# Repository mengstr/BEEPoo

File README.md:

## BEEPoo - Standalone AY3-8912 sound player

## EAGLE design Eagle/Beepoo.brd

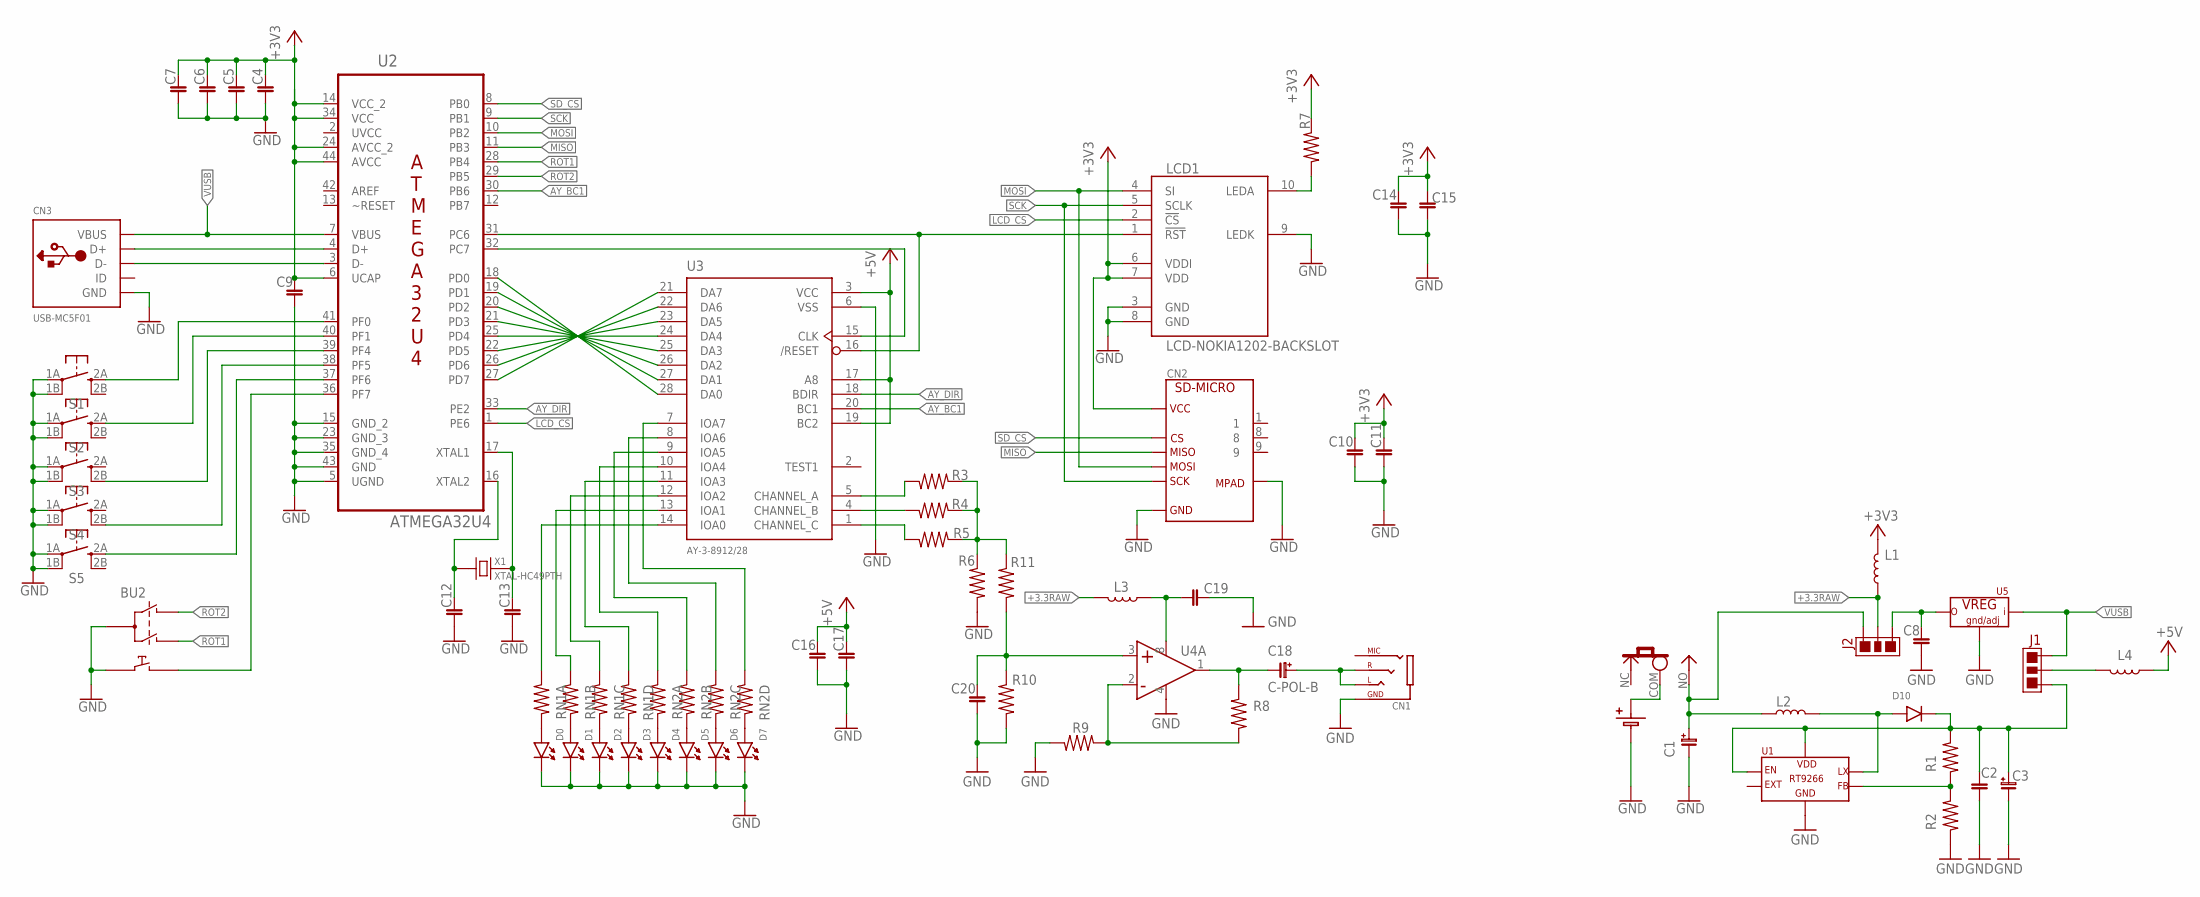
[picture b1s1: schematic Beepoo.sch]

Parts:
BA1: BATTERY2-CR123; BAT-CR123A
BU2: ROTARY
C1: C-POL-C; PANASONIC_C
C2, C4, C5, C6, C7, C11, C12, C13, C15, C17, C20: C-0805; C0805
C3: EEEFK0J101UR; PANASONIC_C
C8, C9, C10, C14, C16, C19: 1u; C0805
C18: C-POL-B; PANASONIC_B
CN1: JACK4PTH; PJ320E
CN2: SD-MICRO; SD-TFP09
CN3: USB-MC5F01; USB-MICRO-MC5F01
D0, D1, D2, D3, D4, D5, D6, D7: LED-0805; LED0805
D10: DIODE-SOD123; SOD123
J1, J2: JUMPER3-1.5MM; JP3-1.5MM
L1, L3, L4: L-0805; L0805
L2: L-BOURNS-SRP7030; IND-BOURNS-SRP7030
LCD1: LCD-NOKIA1202-BACKSLOT; NOKIA1202LCD-BACK-SLOT
R1, R2, R3, R4, R5, R6, R7, R8, R9, R10, R11: R-0805; R0805
RN1, RN2: R-ARR4; RN8P-4R-CRA06S
S1, S2, S3, S4, S5: SWITCH2-12X12PTH; TACT12X12-PTH
SW2: SLIDE1-PCM12; SW-PCM12
U1: RT9266-SOT23; SOT23-6
U2: ATMEGA32U4; TQFP44
U3: AY-3-8912/28; DIL28-6
U4: OPAMP-DUAL-SOIC8; SO08
U5: VREG3-SOT223; SOT223
X1: XTAL-HC49PTH; HC49US

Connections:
+3.3RAW: J2.P$2, L1.1, L3.2
+3V3: C4.2, C5.2, C6.2, C7.2, C9.2, C10.2, C11.2, C14.2, C15.2, CN2.4, L1.2, LCD1.6 (VDDI), LCD1.7 (VDD), R7.1, U2.6 (UCAP), U2.14 (VCC_2), U2.24 (AVCC_2), U2.34 (VCC), U2.44 (AVCC)
+5V: C16.2, C17.2, L4.1, U3.3 (VCC), U3.17 (A8), U3.19 (BC2)
AY_BC1: U2.30 (PB6), U3.20 (BC1)
AY_CLK: U2.32 (PC7), U3.15 (CLK)
AY_DIR: U2.33 (PE2), U3.18 (BDIR)
AY_RESET: LCD1.1 (!RST), U2.31 (PC6), U3.16 (/RESET)
BAT: BA1.POS (POS1), SW2.COM
BAT-SWITCHED: C1.+ (A), J2.P$1, L2.P$1, SW2.NO
GND: BA1.NEG, BU2.Q, BU2.SW1, C1.- (C), C2.2, C3.- (C), C4.1, C5.1, C6.1, C7.1, C8.1, C9.1, C10.1, C11.1, C12.1, C13.1, C14.1, C15.1, C16.1, C17.1, C19.2, C20.1, CN1.G (GND), CN2.GND@1, CN2.GND@2, CN3.P5 (GND), D0.C, D1.C, D2.C, D3.C, D4.C, D5.C, D6.C, D7.C, LCD1.3 (GND), LCD1.8 (GND), LCD1.9 (LEDK), R2.1, R6.2, R9.2, R10.2, S1.1A, S1.1B, S2.1A, S2.1B, S3.1A, S3.1B, S4.1A, S4.1B, S5.1A, S5.1B, U1.3 (GND), U2.5 (UGND), U2.15 (GND_2), U2.23 (GND_3), U2.35 (GND_4), U2.43 (GND), U3.6 (VSS), U4.4 (V-), U5.1 (G/A)
LCD_CS: LCD1.2 (!CS), U2.1 (PE6)
MISO: CN2.7, U2.11 (PB3)
MOSI: CN2.3, LCD1.4 (SI), U2.10 (PB2)
unnamed: D10.A, L2.P$2, U1.4 (LX)
unnamed: C18.+ (A), CN1.L, CN1.R
unnamed: R1.1, R2.2, U1.6 (FB)
unnamed: U2.27 (PD7), U3.21 (DA7)
unnamed: U2.26 (PD6), U3.22 (DA6)
unnamed: U2.22 (PD5), U3.23 (DA5)
unnamed: U2.25 (PD4), U3.24 (DA4)
unnamed: U2.21 (PD3), U3.25 (DA3)
unnamed: U2.20 (PD2), U3.26 (DA2)
unnamed: U2.19 (PD1), U3.27 (DA1)
unnamed: U2.18 (PD0), U3.28 (DA0)
unnamed: C8.2, J2.P$3, U5.2 (OUT), U5.4 (OUT)
unnamed: CN3.P3 (D+), U2.4 (D+)
unnamed: CN3.P2 (D-), U2.3 (D-)
unnamed: C2.1, C3.+ (A), D10.C, J1.P$3, R1.2, U1.1 (EN), U1.5 (VDD)
unnamed: D0.A, RN1.8
unnamed: D1.A, RN1.7
unnamed: D2.A, RN1.6
unnamed: D3.A, RN1.5
unnamed: D4.A, RN2.8
unnamed: C12.2, U2.16 (XTAL2), X1.1
unnamed: D5.A, RN2.7
unnamed: D7.A, RN2.5
unnamed: D6.A, RN2.6
unnamed: RN2.4, U3.7 (IOA7)
unnamed: RN2.3, U3.8 (IOA6)
unnamed: RN2.2, U3.9 (IOA5)
unnamed: RN2.1, U3.10 (IOA4)
unnamed: RN1.4, U3.11 (IOA3)
unnamed: RN1.3, U3.12 (IOA2)
unnamed: RN1.2, U3.13 (IOA1)
unnamed: RN1.1, U3.14 (IOA0)
unnamed: R3.2, U3.5 (CHANNEL_A)
unnamed: R4.2, U3.4 (CHANNEL_B)
unnamed: R5.2, U3.1 (CHANNEL_C)
unnamed: S1.2A, U2.41 (PF0)
unnamed: S2.2A, U2.40 (PF1)
unnamed: S3.2B, U2.39 (PF4)
unnamed: S4.2B, U2.38 (PF5)
unnamed: S5.2A, U2.37 (PF6)
unnamed: R3.1, R4.1, R5.1, R6.1, R11.1
unnamed: BU2.SW2, U2.36 (PF7)
unnamed: C13.2, U2.17 (XTAL1), X1.2
unnamed: LCD1.10 (LEDA), R7.2
unnamed: C18.- (C), R8.1, U4.1 (OUT)
unnamed: C19.1, L3.1, U4.8 (V+)
unnamed: R8.2, R9.1, U4.2 (NEG)
unnamed: J1.P$2, L4.2
unnamed: C20.2, R10.1, R11.2, U4.3 (POS)
ROT1: BU2.Q2, U2.28 (PB4)
ROT2: BU2.Q1, U2.29 (PB5)
SCK: CN2.5, LCD1.5 (SCLK), U2.9 (PB1)
SD_CS: CN2.2, U2.8 (PB0)
UVCC: U2.2 (UVCC)
VUSB: CN3.P1 (VBUS), J1.P$1, U2.7 (VBUS), U5.3 (IN)

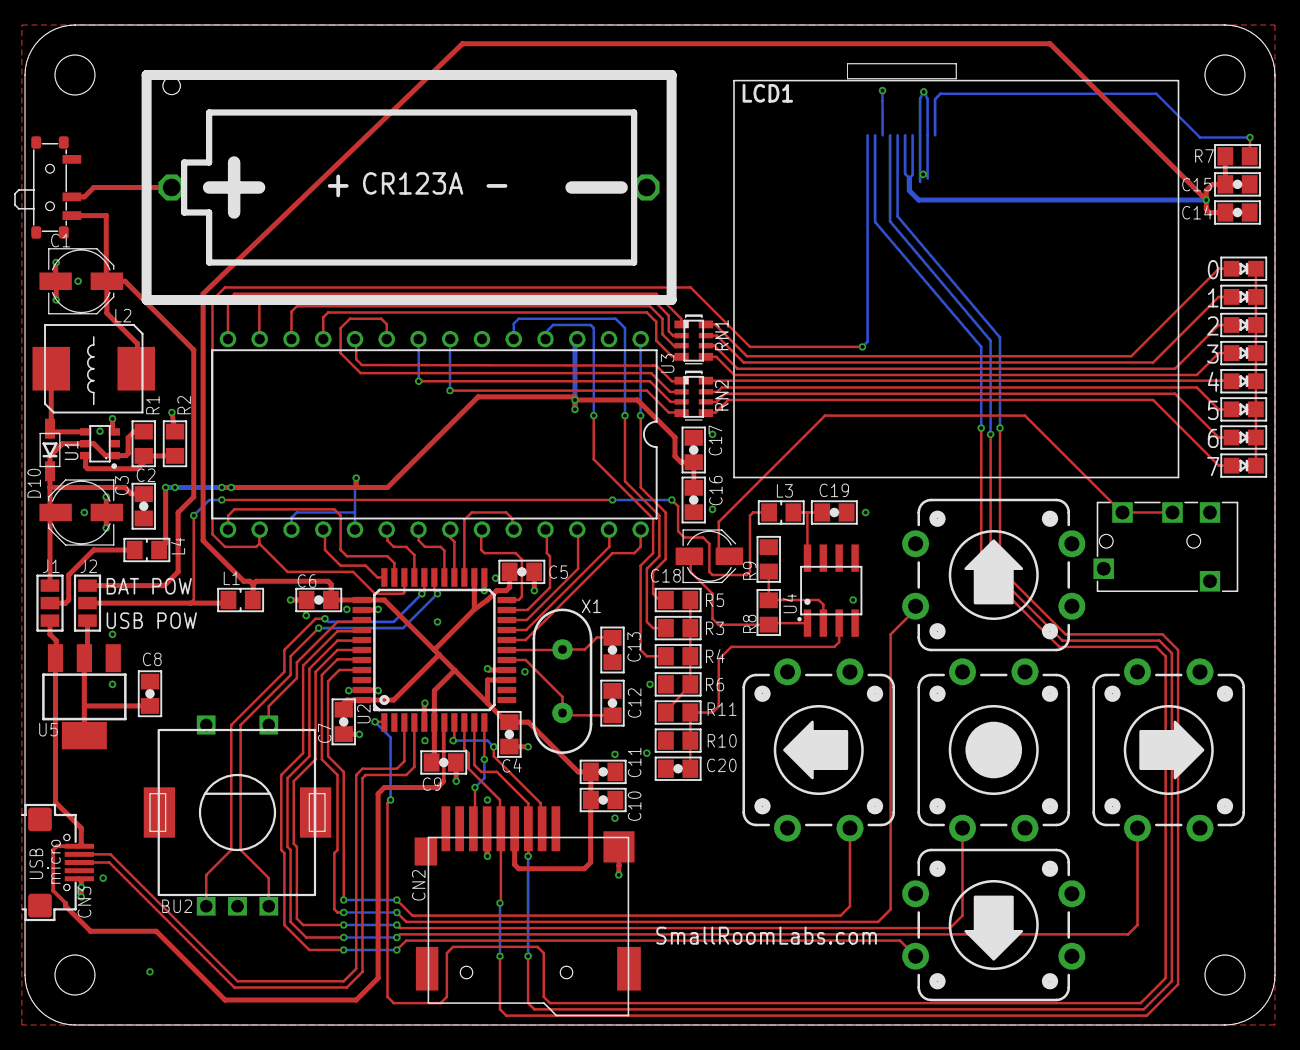
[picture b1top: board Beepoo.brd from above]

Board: 2 copper layers, 100.0 x 80.0 mm, 66 parts (0 on the bottom side), 67 nets.

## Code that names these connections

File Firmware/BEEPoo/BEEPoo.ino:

//
// BEEPoo - Standalone AY-3-8912 player with ATMEGA32U4 with Arduino bootloader
//
// Copyright (c) 2014 SmallRoomLabs / Mats Engstrom - mats.engstrom@gmail.com
// 
// Hardware and Firmware released under the MIT License (MIT) than can be
// found in full in the file named LICENCE in the git repository.
//
// https://github.com/SmallRoomLabs/BEEPoo
//

//
//   PB0 SD_CS       RXLED
//   PB1 SCK         SCK
//   PB2 MOSI        MOSI
//   PB3 MISO        MISO
//   PB4 Rotary Q1   Digital pin 8  (PCINT4)
//   PB5 Rotary Q2   Digital Pin 9 (PCINT5) (PWM)
//   PB6 AY_BC1      Digital Pin 10 (PWM)
//   PB7             Digital pin 11 (PWM)
//   
//   PC6 AY_RESET#   Digital Pin 5 (PWM)
//   PC7 AY_CLK      Digital Pin 13 (PWM)
//   
//   PD0 AY_Data0    Digital pin 3 (SCL)(PWM)
//   PD1 AY_Data1    Digital pin 2 (SDA)
//   PD2 AY_Data2    Digital pin 0 (RX)
//   PD3 AY_Data3    Digital pin 1 (TX)
//   PD4 AY_Data4    Digital pin 4
//   PD5 AY_Data5    TXLED
//   PD6 AY_Data6    Digital pin 12
//   PD7 AY_Data7    Digital Pin 6 (PWM)
// 
//   PE2 AY_Dir      HWB
//   PE6 LCD_CS      Digital pin 7
//   
//   PF0 Button      Analog In 5
//   PF1 Button      Analog In 4
//   PF4 Button      Analog In 3
//   PF5 Button      Analog In 2
//   PF6 Button      Analog In 1
//   PF7 Rotary But  Analog In 0
// 
// 

#include <stdint.h>
#include "rotary.h"
#include "spi.h"
#include "timer1.h"
#include "timer4.h"
#include "ay38912.h"
#include "nokia1202.h"
#include "pff.h"
#include "selectFile.h"
#include "ymplayer.h"
#include "buttons.h"

int AY_RESET    = 5;        // D5
int AY_CLK      = 13;       // D13
int AY_BC1      = 10;       // D10
int DEBUG_LED   = 11;       // D11

#define DEBUGLED_ON  PORTB |= B10000000
#define DEBUGLED_OFF PORTB &= B01111111


//
//
//
void setup() {
  uint8_t mask;

  // PB0 o SD_CS       RXLED
  // PB1 o SCK         SCK
  // PB2 o MOSI        MOSI
  // PB3 i MISO        MISO
  // PB4 i Rotary Q1   Digital pin 8 
  // PB5 i Rotary Q2   Digital Pin 9 (PWM)
  // PB6 o AY_BC1      Digital Pin 10 (PWM)
  // PB7 o DEBUGLED    Digital pin 11 (PWM)
  DDRB=0x00 | (1<<0) | (1<<1) | (1<<2) | (1<<6) | (1<<7);
  // Enable pullup on Rotary Q1/Q3 & MISO
  PORTB=0x00 | (1<<3) | (1<<4) | (1<<5);  

  // PC6 o AY_RESET#   Digital Pin 5 (PWM)
  // PC7 o AY_CLK      Digital Pin 13 (PWM)
  DDRC=0x00 | (1<<6) | (1<<7);
  PORTC=0x00;

  // PD0 o AY_Data0    Digital pin 3 (SCL)(PWM)
  // PD1 o AY_Data1    Digital pin 2 (SDA)
  // PD2 o AY_Data2    Digital pin 0 (RX)
  // PD3 o AY_Data3    Digital pin 1 (TX)
  // PD4 o AY_Data4    Digital pin 4
  // PD5 o AY_Data5    TXLED
  // PD6 o AY_Data6    Digital pin 12
  // PD7 o AY_Data7    Digital Pin 6 (PWM)
  DDRD=0xFF;
  PORTD=0x00;

  // PE2 o AY_Dir      HWB
  // PE6 o LCD_CS      Digital pin 7
  DDRE=0x00 | (1<<2) | (1<<6);
  PORTE=0x00;  

  // PF0 i Button      Analog In 5
  // PF1 i Button      Analog In 4
  // PF4 i Button      Analog In 3
  // PF5 i Button      Analog In 2
  // PF6 i Button      Analog In 1
  // PF7 i Rotary But  Analog In 0
  DDRF=0x00;
  // Enable pullup on all Buttons & Rotary Button
  PORTF=0x00 | (1<<0) | (1<<1) | (1<<4) | (1<<5) | (1<<6) | (1<<7);  

  // Reset AY389-10
  digitalWrite(AY_RESET,LOW);

 // Start timer4 output to D13
  InitTimer4(1000000);
  SetTimer4Duty(512);
  Timer4Start();
  
  // Delay 1 ms before bringing AY out of reset
  delay(1);    
  digitalWrite(AY_RESET,HIGH);

  // Enable PORT A, and the thre tone channels on the AY-3-8912 
  // and turn off all leds
  AyRegister(AY_ENABLE,B01111000);
  for (mask=0x01; mask; mask*=2) {
    AyPort(mask);
    delay(25);
  }
  for (mask=0x40; mask; mask/=2) {
    AyPort(mask);
    delay(25);
  }
  AyPort(0x00); 

  // Turn on interrupts for Rotary Encoder
  PCMSK0 |= (1<<PCINT4) | (1<<PCINT5);      //enable encoder pins interrupt sources
  EICRB |= (1<<ISC40) | (1<<ISC50);
  PCICR |= ( 1<<PCIE0 );

  InitTimer1(64286);  

  DEBUGLED_ON;
}



//
// Handle the 50Hz timer1 interrupt
//
ISR(TIMER1_OVF_vect) {
  IrqTimer1();
}


//
// Currently we only have one interrupt source
// so we can assume it's a rotary encoder interrupt
//
ISR(PCINT0_vect) {
  IrqRotaryEncoder();
}









FATFS  fs;


//
//
//
void loop() {
  int res;
  int i;
  char filename[32];

  LcdInit();

  LcdXY(0,0);LcdString("Mount=");
  res=pf_mount(&fs);
  LcdCharacter(48+res);
  delay(500);

  SelectFile(filename);
  LcdClear();
  LcdString(filename);
  YmPlay(filename);

  DEBUGLED_OFF;
  for (;;) {
      delay(1);
      AyPort(rotaryValue);
      AyRegister(AY_CH_A_FINETUNE, rand()&0xFF);
//      AyRegister(AY_CH_A_COARSETUNE, 1);
  }
}

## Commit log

2014-11-11 Added non-functional firmware
2014-11-11 Add reset to LCD. Connect A8 of AY to VCC
2014-11-11 Add image of devel board
2014-11-11 Reads SD card. Beeps in AY
2014-11-12 Add rotary encoder irq handler
2014-11-12 Reads hardcoded filename and plays it
2014-11-17 Selection of file to play
2014-11-18 Select and play any ym-file works ok

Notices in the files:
parts and their libraries:
SmallRoomLabs: Copyright(c) 2011 Mats Engstrom - mats@smallroomlabs.com
SmallRoomLabs: http://creativecommons.org/licenses/by-sa/3.0
SmallRoomLabs: STANDARD FRAME w. Copyright & License info
